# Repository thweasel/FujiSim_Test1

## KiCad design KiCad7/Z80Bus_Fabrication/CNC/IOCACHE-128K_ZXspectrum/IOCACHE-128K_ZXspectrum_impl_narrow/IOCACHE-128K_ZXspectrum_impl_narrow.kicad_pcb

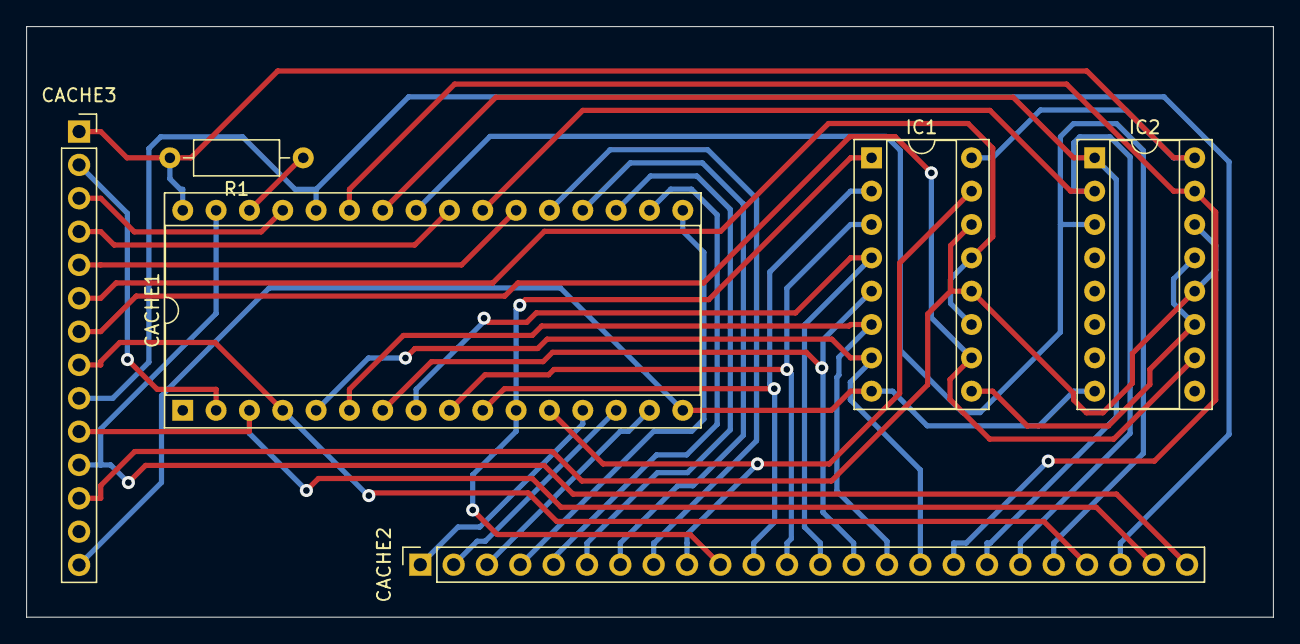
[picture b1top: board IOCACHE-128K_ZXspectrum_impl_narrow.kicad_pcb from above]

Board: 2 copper layers, 95.0 x 45.0 mm, 6 parts (0 on the bottom side), 35 nets.

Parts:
CACHE1: AS6C1008-55PCN; DIP-32_W15.24mm_Socket
CACHE2: Conn_01x24_Socket; PinSocket_1x24_P2.54mm_Vertical
CACHE3: Conn_01x14_Socket; PinSocket_1x14_P2.54mm_Vertical
IC1, IC2: 74HC590N; DIP-16_W7.62mm_Socket
R1: 10K; R_Axial_DIN0207_L6.3mm_D2.5mm_P10.16mm_Horizontal

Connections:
+5V: CACHE1.32 (VCC), CACHE3.1, IC1.16 (VCC), IC2.16 (VCC), R1.2
/IOCACHE-128K_ZXspectrum/CACHE_CE2: CACHE1.30 (CE2#), R1.1
/IOCACHE-128K_ZXspectrum/CACHE_CONTROL.A16: CACHE1.2 (A16), CACHE3.2
/IOCACHE-128K_ZXspectrum/CACHE_CONTROL.CS: CACHE1.22 (CE#), CACHE3.5
/IOCACHE-128K_ZXspectrum/CACHE_CONTROL.DATASTATUS+PERM_Z80_IORQ: CACHE3.6, IC1.11 (CPC), IC1.13 (CPR)
/IOCACHE-128K_ZXspectrum/CACHE_CONTROL.OE: CACHE1.24 (OE#), CACHE3.4
/IOCACHE-128K_ZXspectrum/CACHE_CONTROL.WE: CACHE1.29 (WE#), CACHE3.3
/IOCACHE-128K_ZXspectrum/CACHE_DATASTATUS: CACHE3.12, IC1.12 (~CE), IC1.14 (~OE), IC2.12 (~CE), IC2.14 (~OE)
/IOCACHE-128K_ZXspectrum/LOCAL_A0: CACHE1.12 (A0), CACHE2.9, IC1.15 (Q0)
/IOCACHE-128K_ZXspectrum/LOCAL_A1: CACHE1.11 (A1), CACHE2.10, IC1.1 (Q1)
/IOCACHE-128K_ZXspectrum/LOCAL_A2: CACHE1.10 (A2), CACHE2.11, IC1.2 (Q2)
/IOCACHE-128K_ZXspectrum/LOCAL_A3: CACHE1.9 (A3), CACHE2.12, IC1.3 (Q3)
/IOCACHE-128K_ZXspectrum/LOCAL_A4: CACHE1.8 (A4), CACHE2.13, IC1.4 (Q4)
/IOCACHE-128K_ZXspectrum/LOCAL_A5: CACHE1.7 (A5), CACHE2.14, IC1.5 (Q5)
/IOCACHE-128K_ZXspectrum/LOCAL_A6: CACHE1.6 (A6), CACHE2.15, IC1.6 (Q6)
/IOCACHE-128K_ZXspectrum/LOCAL_A7: CACHE1.5 (A7), CACHE2.16, IC1.7 (Q7)
/IOCACHE-128K_ZXspectrum/LOCAL_A8: CACHE1.27 (A8), CACHE2.17, IC2.15 (Q0)
/IOCACHE-128K_ZXspectrum/LOCAL_A9: CACHE1.26 (A9), CACHE2.18, IC2.1 (Q1)
/IOCACHE-128K_ZXspectrum/LOCAL_A10: CACHE1.23 (A10), CACHE2.19, IC2.2 (Q2)
/IOCACHE-128K_ZXspectrum/LOCAL_A11: CACHE1.25 (A11), CACHE2.20, IC2.3 (Q3)
/IOCACHE-128K_ZXspectrum/LOCAL_A12: CACHE1.4 (A12), CACHE2.21, CACHE3.8
/IOCACHE-128K_ZXspectrum/LOCAL_A13: CACHE1.28 (A13), CACHE2.22, CACHE3.9
/IOCACHE-128K_ZXspectrum/LOCAL_A14: CACHE1.3 (A14), CACHE2.23, CACHE3.10
/IOCACHE-128K_ZXspectrum/LOCAL_A15: CACHE1.31 (A15), CACHE2.24, CACHE3.11
/IOCACHE-128K_ZXspectrum/LOCAL_D0: CACHE1.13 (DQ0), CACHE2.1
/IOCACHE-128K_ZXspectrum/LOCAL_D1: CACHE1.14 (DQ1), CACHE2.2
/IOCACHE-128K_ZXspectrum/LOCAL_D2: CACHE1.15 (DQ2), CACHE2.3
/IOCACHE-128K_ZXspectrum/LOCAL_D3: CACHE1.17 (DQ3), CACHE2.4
/IOCACHE-128K_ZXspectrum/LOCAL_D4: CACHE1.18 (DQ4), CACHE2.5
/IOCACHE-128K_ZXspectrum/LOCAL_D5: CACHE1.19 (DQ5), CACHE2.6
/IOCACHE-128K_ZXspectrum/LOCAL_D6: CACHE1.20 (DQ6), CACHE2.7
/IOCACHE-128K_ZXspectrum/LOCAL_D7: CACHE1.21 (DQ7), CACHE2.8
/IOCACHE-128K_ZXspectrum/Z80_HARDLOCK: CACHE3.7, IC1.10 (~MRC), IC2.10 (~MRC)
GND: CACHE1.16 (VSS), CACHE3.14, IC1.8 (GND), IC2.8 (GND)
unnamed: IC1.9 (~RCO), IC2.11 (CPC), IC2.13 (CPR)

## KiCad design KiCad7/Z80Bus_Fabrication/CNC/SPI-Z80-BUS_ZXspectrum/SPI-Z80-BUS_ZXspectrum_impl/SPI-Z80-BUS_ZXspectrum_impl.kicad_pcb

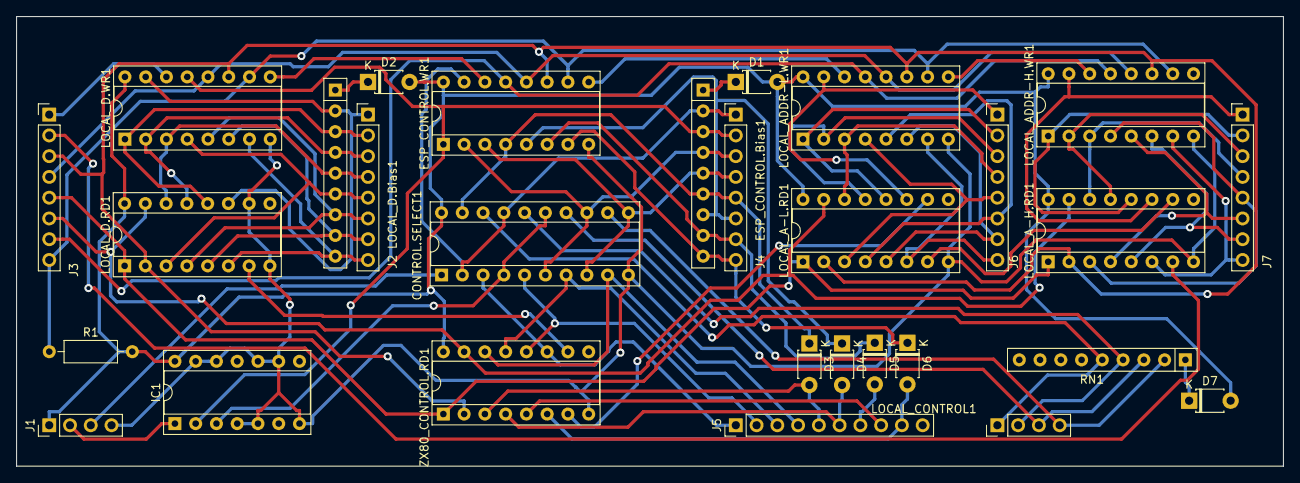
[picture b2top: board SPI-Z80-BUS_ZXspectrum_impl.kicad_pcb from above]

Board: 2 copper layers, 155.0 x 55.0 mm, 29 parts (0 on the bottom side), 67 nets.

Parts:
CONTROL.SELECT1: 74HC244N; DIP-20_W7.62mm_Socket
D1, D2, D3, D4, D5, D6, D7: 1N4148; D_T-1_P5.08mm_Horizontal
ESP_CONTROL.Bias1: 4609M-101-103LF; R_Array_SIP9
ESP_CONTROL.WR1: 74595N; DIP-16_W7.62mm_Socket
IC1: 74HC32N; DIP-14_W7.62mm_Socket
J1: PinHeader_2.54mm; PinHeader_1x04_P2.54mm_Vertical
J2: LOCAL_D; PinHeader_1x08_P2.54mm_Vertical
J3: ESP_SPI_INT; PinHeader_1x08_P2.54mm_Vertical
J4: ESP_CONTROL; PinHeader_1x08_P2.54mm_Vertical
J5: Z80_CONTROL; PinHeader_1x10_P2.54mm_Vertical
J6: LOCAL_A-L; PinHeader_1x08_P2.54mm_Vertical
J7: LOCAL_A-H; PinHeader_1x08_P2.54mm_Vertical
LOCAL_A-H.RD1: 74HC165N; DIP-16_W7.62mm_Socket
LOCAL_A-L.RD1: 74HC165N; DIP-16_W7.62mm_Socket
LOCAL_ADDR-H.WR1: 74595N; DIP-16_W7.62mm_Socket
LOCAL_ADDR-L.WR1: 74595N; DIP-16_W7.62mm_Socket
LOCAL_CONTROL1: LOCAL_CONTROL; PinHeader_1x04_P2.54mm_Vertical
LOCAL_D.Bias1: 4609M-101-103LF; R_Array_SIP9
LOCAL_D.RD1: 74HC165N; DIP-16_W7.62mm_Socket
LOCAL_D.WR1: 74595N; DIP-16_W7.62mm_Socket
R1: 22K; R_Axial_DIN0207_L6.3mm_D2.5mm_P10.16mm_Horizontal
RN1: LOCAL_CONTROL.Bias; R_Array_SIP9
ZX80_CONTROL.RD1: 74HC165N; DIP-16_W7.62mm_Socket

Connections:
+5V: CONTROL.SELECT1.20 (VCC), D1.2 (A), D2.2 (A), D7.2 (A), ESP_CONTROL.WR1.16 (VCC), IC1.14 (VCC), J1.1, LOCAL_A-H.RD1.16 (VCC), LOCAL_A-L.RD1.16 (VCC), LOCAL_ADDR-H.WR1.16 (VCC), LOCAL_ADDR-L.WR1.16 (VCC), LOCAL_D.RD1.16 (VCC), LOCAL_D.WR1.16 (VCC), R1.2, ZX80_CONTROL.RD1.16 (VCC)
/SPI-Z80-BUS/!ESP_HARDLOCK: CONTROL.SELECT1.1 (1OE), J1.3
/SPI-Z80-BUS/ESP_CONTROL.BUSRQ: CONTROL.SELECT1.19 (2OE), D3.1 (K), ESP_CONTROL.Bias1.6 (R5), ESP_CONTROL.WR1.4 (QE), J4.5
/SPI-Z80-BUS/ESP_CONTROL.IORQ: CONTROL.SELECT1.6 (1A2), CONTROL.SELECT1.13 (2A2), ESP_CONTROL.Bias1.4 (R3), ESP_CONTROL.WR1.2 (QC), J4.3
/SPI-Z80-BUS/ESP_CONTROL.MEMRQ: CONTROL.SELECT1.8 (1A3), CONTROL.SELECT1.11 (2A3), ESP_CONTROL.Bias1.5 (R4), ESP_CONTROL.WR1.3 (QD), J4.4
/SPI-Z80-BUS/ESP_CONTROL.NMI: D6.1 (K), ESP_CONTROL.Bias1.9 (R8), ESP_CONTROL.WR1.7 (QH), J4.8
/SPI-Z80-BUS/ESP_CONTROL.RD: CONTROL.SELECT1.2 (1A0), CONTROL.SELECT1.17 (2A0), ESP_CONTROL.Bias1.2 (R1), ESP_CONTROL.WR1.15 (QA), J4.1
/SPI-Z80-BUS/ESP_CONTROL.ROMCS: D5.1 (K), ESP_CONTROL.Bias1.8 (R7), ESP_CONTROL.WR1.6 (QG), J4.7
/SPI-Z80-BUS/ESP_CONTROL.WAIT: D4.1 (K), ESP_CONTROL.Bias1.7 (R6), ESP_CONTROL.WR1.5 (QF), J4.6
/SPI-Z80-BUS/ESP_CONTROL.WR: ESP_CONTROL.Bias1.3 (R2), ESP_CONTROL.WR1.1 (QB), IC1.2, J4.2, LOCAL_D.WR1.13 (~OE)
/SPI-Z80-BUS/ESP_PULSE: IC1.1, J1.2
/SPI-Z80-BUS/ESP_SPI_INT.CE: J3.6, LOCAL_A-H.RD1.15 (~CE), LOCAL_A-L.RD1.15 (~CE), LOCAL_D.RD1.15 (~CE), ZX80_CONTROL.RD1.15 (~CE)
/SPI-Z80-BUS/ESP_SPI_INT.MISO: J3.2, LOCAL_A-H.RD1.7 (~Q7)
/SPI-Z80-BUS/ESP_SPI_INT.MOSI: J3.1, LOCAL_D.WR1.14 (SER)
/SPI-Z80-BUS/ESP_SPI_INT.MR: ESP_CONTROL.WR1.10 (~SRCLR), J3.8, LOCAL_ADDR-H.WR1.10 (~SRCLR), LOCAL_ADDR-L.WR1.10 (~SRCLR), LOCAL_D.WR1.10 (~SRCLR), R1.1
/SPI-Z80-BUS/ESP_SPI_INT.OE: ESP_CONTROL.WR1.13 (~OE), J3.7, LOCAL_ADDR-H.WR1.13 (~OE), LOCAL_ADDR-L.WR1.13 (~OE)
/SPI-Z80-BUS/ESP_SPI_INT.PL: J3.5, LOCAL_A-H.RD1.1 (~PL), LOCAL_A-L.RD1.1 (~PL), LOCAL_D.RD1.1 (~PL), ZX80_CONTROL.RD1.1 (~PL)
/SPI-Z80-BUS/ESP_SPI_INT.SCK: ESP_CONTROL.WR1.11 (SRCLK), J3.3, LOCAL_A-H.RD1.2 (CP), LOCAL_A-L.RD1.2 (CP), LOCAL_ADDR-H.WR1.11 (SRCLK), LOCAL_ADDR-L.WR1.11 (SRCLK), LOCAL_D.RD1.2 (CP), LOCAL_D.WR1.11 (SRCLK), ZX80_CONTROL.RD1.2 (CP)
/SPI-Z80-BUS/ESP_SPI_INT.STC: ESP_CONTROL.WR1.12 (RCLK), J3.4, LOCAL_ADDR-H.WR1.12 (RCLK), LOCAL_ADDR-L.WR1.12 (RCLK), LOCAL_D.WR1.12 (RCLK)
/SPI-Z80-BUS/LOCAL_A0: J6.1, LOCAL_A-L.RD1.11 (D0), LOCAL_ADDR-L.WR1.15 (QA)
/SPI-Z80-BUS/LOCAL_A1: J6.2, LOCAL_A-L.RD1.12 (D1), LOCAL_ADDR-L.WR1.1 (QB)
/SPI-Z80-BUS/LOCAL_A2: J6.3, LOCAL_A-L.RD1.13 (D2), LOCAL_ADDR-L.WR1.2 (QC)
/SPI-Z80-BUS/LOCAL_A3: J6.4, LOCAL_A-L.RD1.14 (D3), LOCAL_ADDR-L.WR1.3 (QD)
/SPI-Z80-BUS/LOCAL_A4: J6.5, LOCAL_A-L.RD1.3 (D4), LOCAL_ADDR-L.WR1.4 (QE)
/SPI-Z80-BUS/LOCAL_A5: J6.6, LOCAL_A-L.RD1.4 (D5), LOCAL_ADDR-L.WR1.5 (QF)
/SPI-Z80-BUS/LOCAL_A6: J6.7, LOCAL_A-L.RD1.5 (D6), LOCAL_ADDR-L.WR1.6 (QG)
/SPI-Z80-BUS/LOCAL_A7: J6.8, LOCAL_A-L.RD1.6 (D7), LOCAL_ADDR-L.WR1.7 (QH)
/SPI-Z80-BUS/LOCAL_A8: J7.1, LOCAL_A-H.RD1.11 (D0), LOCAL_ADDR-H.WR1.15 (QA)
/SPI-Z80-BUS/LOCAL_A9: J7.2, LOCAL_A-H.RD1.12 (D1), LOCAL_ADDR-H.WR1.1 (QB)
/SPI-Z80-BUS/LOCAL_A10: J7.3, LOCAL_A-H.RD1.13 (D2), LOCAL_ADDR-H.WR1.2 (QC)
/SPI-Z80-BUS/LOCAL_A11: J7.4, LOCAL_A-H.RD1.14 (D3), LOCAL_ADDR-H.WR1.3 (QD)
/SPI-Z80-BUS/LOCAL_A12: J7.5, LOCAL_A-H.RD1.3 (D4), LOCAL_ADDR-H.WR1.4 (QE)
/SPI-Z80-BUS/LOCAL_A13: J7.6, LOCAL_A-H.RD1.4 (D5), LOCAL_ADDR-H.WR1.5 (QF)
/SPI-Z80-BUS/LOCAL_A14: J7.7, LOCAL_A-H.RD1.5 (D6), LOCAL_ADDR-H.WR1.6 (QG)
/SPI-Z80-BUS/LOCAL_A15: J7.8, LOCAL_A-H.RD1.6 (D7), LOCAL_ADDR-H.WR1.7 (QH)
/SPI-Z80-BUS/LOCAL_CONTROL.IORQ: CONTROL.SELECT1.14 (1Y2), LOCAL_CONTROL1.3, RN1.3 (R2)
/SPI-Z80-BUS/LOCAL_CONTROL.MEMRQ: CONTROL.SELECT1.12 (1Y3), LOCAL_CONTROL1.4, RN1.2 (R1)
/SPI-Z80-BUS/LOCAL_CONTROL.RD: CONTROL.SELECT1.18 (1Y0), LOCAL_CONTROL1.1, RN1.5 (R4)
/SPI-Z80-BUS/LOCAL_CONTROL.WR: CONTROL.SELECT1.16 (1Y1), LOCAL_CONTROL1.2, RN1.4 (R3)
/SPI-Z80-BUS/LOCAL_D0: J2.1, LOCAL_D.Bias1.2 (R1), LOCAL_D.RD1.11 (D0), LOCAL_D.WR1.15 (QA)
/SPI-Z80-BUS/LOCAL_D1: J2.2, LOCAL_D.Bias1.3 (R2), LOCAL_D.RD1.12 (D1), LOCAL_D.WR1.1 (QB)
/SPI-Z80-BUS/LOCAL_D2: J2.3, LOCAL_D.Bias1.4 (R3), LOCAL_D.RD1.13 (D2), LOCAL_D.WR1.2 (QC)
/SPI-Z80-BUS/LOCAL_D3: J2.4, LOCAL_D.Bias1.5 (R4), LOCAL_D.RD1.14 (D3), LOCAL_D.WR1.3 (QD)
/SPI-Z80-BUS/LOCAL_D4: J2.5, LOCAL_D.Bias1.6 (R5), LOCAL_D.RD1.3 (D4), LOCAL_D.WR1.4 (QE)
/SPI-Z80-BUS/LOCAL_D5: J2.6, LOCAL_D.Bias1.7 (R6), LOCAL_D.RD1.4 (D5), LOCAL_D.WR1.5 (QF)
/SPI-Z80-BUS/LOCAL_D6: J2.7, LOCAL_D.Bias1.8 (R7), LOCAL_D.RD1.5 (D6), LOCAL_D.WR1.6 (QG)
/SPI-Z80-BUS/LOCAL_D7: J2.8, LOCAL_D.Bias1.9 (R8), LOCAL_D.RD1.6 (D7), LOCAL_D.WR1.7 (QH)
/SPI-Z80-BUS/Z80_CONTROL.BUSACK: J5.8, ZX80_CONTROL.RD1.5 (D6)
/SPI-Z80-BUS/Z80_CONTROL.BUSRQ: D3.2 (A), J5.5, ZX80_CONTROL.RD1.3 (D4)
/SPI-Z80-BUS/Z80_CONTROL.IORQ: CONTROL.SELECT1.7 (2Y2), J5.3, ZX80_CONTROL.RD1.13 (D2)
/SPI-Z80-BUS/Z80_CONTROL.MEMRQ: CONTROL.SELECT1.9 (2Y3), J5.4, ZX80_CONTROL.RD1.14 (D3)
/SPI-Z80-BUS/Z80_CONTROL.NMI: D6.2 (A), J5.9, ZX80_CONTROL.RD1.6 (D7)
/SPI-Z80-BUS/Z80_CONTROL.RD: CONTROL.SELECT1.3 (2Y0), J5.1, ZX80_CONTROL.RD1.11 (D0)
/SPI-Z80-BUS/Z80_CONTROL.ROMCS: D5.2 (A), J5.7
/SPI-Z80-BUS/Z80_CONTROL.WAIT: D4.2 (A), J5.6, ZX80_CONTROL.RD1.4 (D5)
/SPI-Z80-BUS/Z80_CONTROL.WR: CONTROL.SELECT1.5 (2Y1), J5.2, ZX80_CONTROL.RD1.12 (D1)
GND: CONTROL.SELECT1.10 (GND), ESP_CONTROL.WR1.8 (GND), IC1.4, IC1.5, IC1.7 (GND), IC1.9, IC1.10, IC1.12, IC1.13, J1.4, LOCAL_A-H.RD1.8 (GND), LOCAL_A-L.RD1.8 (GND), LOCAL_ADDR-H.WR1.8 (GND), LOCAL_ADDR-L.WR1.8 (GND), LOCAL_D.RD1.8 (GND), LOCAL_D.RD1.10 (DS), LOCAL_D.WR1.8 (GND), ZX80_CONTROL.RD1.8 (GND)
unnamed: CONTROL.SELECT1.4 (1A1), CONTROL.SELECT1.15 (2A1), IC1.3
unnamed: D1.1 (K), ESP_CONTROL.Bias1.1 (common)
unnamed: D2.1 (K), LOCAL_D.Bias1.1 (common)
unnamed: D7.1 (K), RN1.1 (common)
unnamed: ESP_CONTROL.WR1.9 (QH'), LOCAL_ADDR-L.WR1.14 (SER)
unnamed: ESP_CONTROL.WR1.14 (SER), LOCAL_D.WR1.9 (QH')
unnamed: LOCAL_A-H.RD1.10 (DS), LOCAL_A-L.RD1.7 (~Q7)
unnamed: LOCAL_A-L.RD1.10 (DS), ZX80_CONTROL.RD1.7 (~Q7)
unnamed: LOCAL_ADDR-H.WR1.14 (SER), LOCAL_ADDR-L.WR1.9 (QH')
unnamed: LOCAL_D.RD1.7 (~Q7), ZX80_CONTROL.RD1.10 (DS)

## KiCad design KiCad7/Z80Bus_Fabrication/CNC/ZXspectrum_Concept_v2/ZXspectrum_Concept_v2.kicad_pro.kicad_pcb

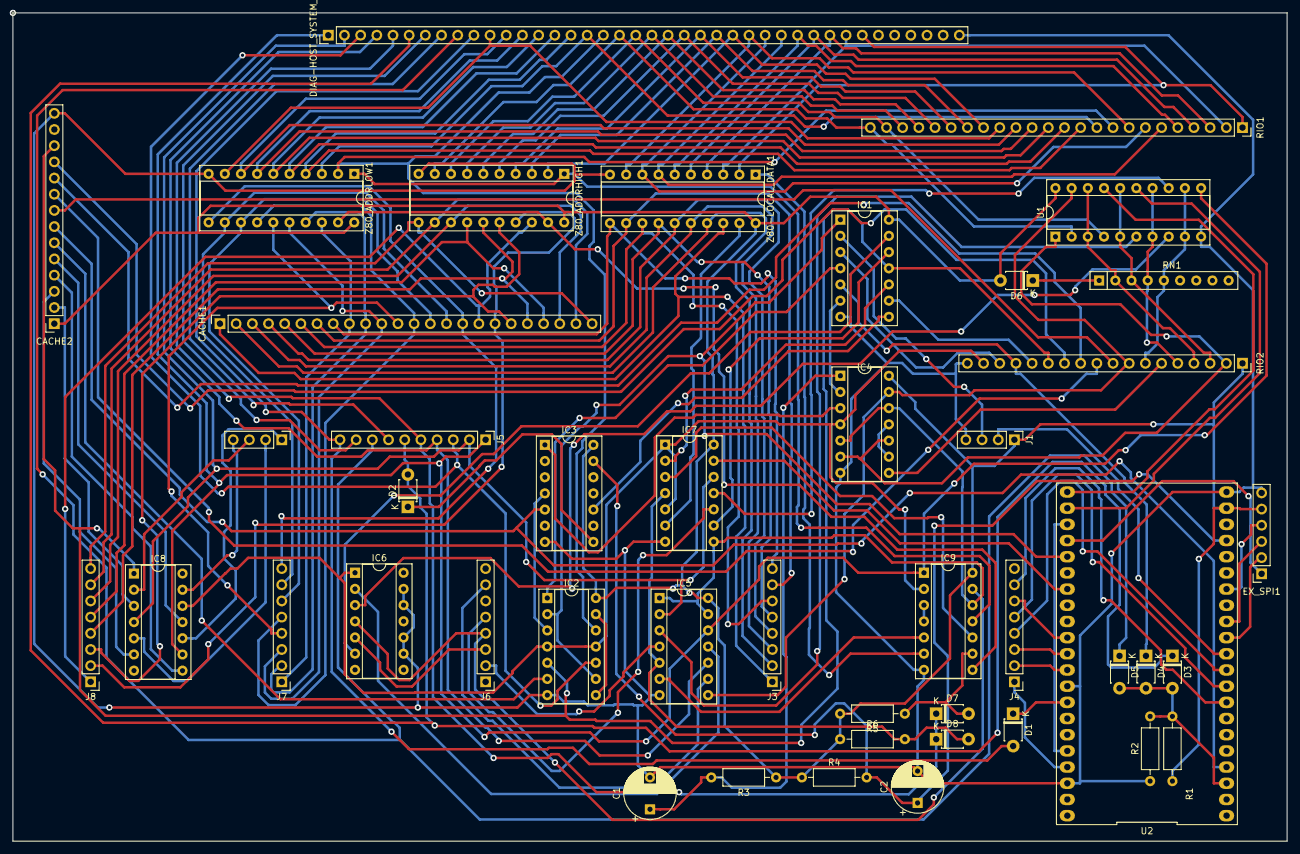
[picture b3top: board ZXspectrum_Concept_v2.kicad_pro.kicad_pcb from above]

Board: 2 copper layers, 200.0 x 130.0 mm, 45 parts (0 on the bottom side), 139 nets.

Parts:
C1, C2: 10UF; CP_Radial_D8.0mm_P5.00mm
CACHE1: Conn_01x24_Socket; PinSocket_1x24_P2.54mm_Vertical
CACHE2: Conn_01x14_Socket; PinSocket_1x14_P2.54mm_Vertical
D1, D2, D3, D4, D5, D6, D7, D8: 1N4148; D_T-1_P5.08mm_Horizontal
DIAG-HOST_SYSTEM_BUS1: DIAG-HOST_SYSTEM_BUS; PinHeader_1x40_P2.54mm_Vertical
EX_SPI1: PinSocket_2.54mm; PinSocket_1x06_P2.54mm_Vertical
IC1: 7404N; DIP-14_W7.62mm_Socket
IC2, IC5, IC7, IC9: 74HC32N; DIP-14_W7.62mm_Socket
IC3: 7474N; DIP-14_W7.62mm_Socket
IC4, IC6, IC8: 74HC08N; DIP-14_W7.62mm_Socket
J1: PinHeader_2.54mm; PinHeader_1x04_P2.54mm_Vertical
J3: LOCAL_D; PinHeader_1x08_P2.54mm_Vertical
J4: ESP_SPI_INT; PinHeader_1x08_P2.54mm_Vertical
J5: Z80_CONTROL; PinHeader_1x10_P2.54mm_Vertical
J6: ESP_CONTROL; PinHeader_1x08_P2.54mm_Vertical
J7: LOCAL_A-L; PinHeader_1x08_P2.54mm_Vertical
J8: LOCAL_A-H; PinHeader_1x08_P2.54mm_Vertical
LOCAL_CONTROL1: LOCAL_CONTROL; PinHeader_1x04_P2.54mm_Vertical
R1, R2, R3, R4: 22K; R_Axial_DIN0207_L6.3mm_D2.5mm_P10.16mm_Horizontal
R5, R6: 10K; R_Axial_DIN0207_L6.3mm_D2.5mm_P10.16mm_Horizontal
RIO1: Conn_01x24_Socket; PinSocket_1x24_P2.54mm_Vertical
RIO2: Conn_01x18_Socket; PinSocket_1x18_P2.54mm_Vertical
RN1: 4609M-101-103LF; R_Array_SIP9
U1: 74HC244N; DIP-20_W7.62mm_Socket
U2: FREENOVE_ESP32-WROVER-DEV
Z80-LOCAL_DATA1, Z80_ADDRHIGH1, Z80_ADDRLOW1: 74HC245N; DIP-20_W7.62mm_Socket

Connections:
+5V: CACHE2.1, D6.2 (A), EX_SPI1.5, IC1.14 (VCC), IC2.14 (VCC), IC3.14 (VCC), IC4.14 (VCC), IC5.14 (VCC), IC7.14 (VCC), IC9.14 (VCC), J1.1, R1.2, R3.1, R4.1, R5.2, R6.1, RIO2.1, U1.20 (VCC), U2.20 (+5V), Z80-LOCAL_DATA1.20 (VCC), Z80_ADDRHIGH1.20 (VCC), Z80_ADDRLOW1.20 (VCC)
/CACHE connector/CACHE_CONTROL.A16: CACHE2.2, IC8.3
/CACHE connector/CACHE_CONTROL.CS: CACHE2.5, IC8.11
/CACHE connector/CACHE_CONTROL.DATASTATUS+PERM_Z80_IORQ: CACHE2.6, IC2.6
/CACHE connector/CACHE_CONTROL.OE: CACHE2.4, IC8.8
/CACHE connector/CACHE_CONTROL.WE: CACHE2.3, IC8.6
/CACHE connector/CACHE_DATASTATUS: CACHE2.12, IC1.11, IC2.5, IC8.1, RIO2.13
/CACHE connector/CACHE_SEL_0: CACHE2.8, RIO2.9
/CACHE connector/CACHE_SEL_1: CACHE2.9, RIO2.10
/CACHE connector/CACHE_SEL_2: CACHE2.10, RIO2.11
/CACHE connector/CACHE_SEL_3: CACHE2.11, RIO2.12
/CACHE connector/LOCAL_A0: CACHE1.9, J7.1, Z80_ADDRLOW1.18 (B0)
/CACHE connector/LOCAL_A1: CACHE1.10, J7.2, Z80_ADDRLOW1.17 (B1)
/CACHE connector/LOCAL_A2: CACHE1.11, J7.3, Z80_ADDRLOW1.16 (B2)
/CACHE connector/LOCAL_A3: CACHE1.12, J7.4, Z80_ADDRLOW1.15 (B3)
/CACHE connector/LOCAL_A4: CACHE1.13, J7.5, Z80_ADDRLOW1.14 (B4)
/CACHE connector/LOCAL_A5: CACHE1.14, J7.6, Z80_ADDRLOW1.13 (B5)
/CACHE connector/LOCAL_A6: CACHE1.15, J7.7, Z80_ADDRLOW1.12 (B6)
/CACHE connector/LOCAL_A7: CACHE1.16, J7.8, Z80_ADDRLOW1.11 (B7)
/CACHE connector/LOCAL_A8: CACHE1.17, J8.1, Z80_ADDRHIGH1.18 (B0)
/CACHE connector/LOCAL_A9: CACHE1.18, J8.2, Z80_ADDRHIGH1.17 (B1)
/CACHE connector/LOCAL_A10: CACHE1.19, J8.3, Z80_ADDRHIGH1.16 (B2)
/CACHE connector/LOCAL_A11: CACHE1.20, J8.4, Z80_ADDRHIGH1.15 (B3)
/CACHE connector/LOCAL_A12: CACHE1.21, J8.5, Z80_ADDRHIGH1.14 (B4)
/CACHE connector/LOCAL_A13: CACHE1.22, J8.6, Z80_ADDRHIGH1.13 (B5)
/CACHE connector/LOCAL_A14: CACHE1.23, J8.7, Z80_ADDRHIGH1.12 (B6)
/CACHE connector/LOCAL_A15: CACHE1.24, J8.8, Z80_ADDRHIGH1.11 (B7)
/CACHE connector/LOCAL_D0: CACHE1.1, J3.1, Z80-LOCAL_DATA1.18 (B0)
/CACHE connector/LOCAL_D1: CACHE1.2, J3.2, Z80-LOCAL_DATA1.17 (B1)
/CACHE connector/LOCAL_D2: CACHE1.3, J3.3, Z80-LOCAL_DATA1.16 (B2)
/CACHE connector/LOCAL_D3: CACHE1.4, J3.4, Z80-LOCAL_DATA1.15 (B3)
/CACHE connector/LOCAL_D4: CACHE1.5, J3.5, Z80-LOCAL_DATA1.14 (B4)
/CACHE connector/LOCAL_D5: CACHE1.6, J3.6, Z80-LOCAL_DATA1.13 (B5)
/CACHE connector/LOCAL_D6: CACHE1.7, J3.7, Z80-LOCAL_DATA1.12 (B6)
/CACHE connector/LOCAL_D7: CACHE1.8, J3.8, Z80-LOCAL_DATA1.11 (B7)
/CACHE connector/Z80_HARDLOCK: CACHE2.7, IC3.5 (Q), U2.4 (GPIO39)
/CORE/ESP_HARDLOCK: IC1.1, IC2.2, IC2.9, U2.26 (GPIO2)
/CORE/ESP_INT: D3.2 (A), D4.2 (A), D5.2 (A), R1.1, R2.2, U2.3 (GPIO36)
/CORE/ESP_PULSE: J1.2, U2.11 (GPIO27)
/CORE/ESP_ROMSEL_0: U1.15 (2A1), U2.23 (GPIO7)
/CORE/ESP_ROMSEL_1: U1.17 (2A0), U2.22 (GPIO6)
/CORE/ESP_ROM_WR_PROTECT: IC7.13, U2.28 (GPIO4)
/CORE/ESP_SPI_INT.CE: J4.6, U2.31 (GPIO5)
/CORE/ESP_SPI_INT.MISO: J4.2, U2.33 (GPIO19)
/CORE/ESP_SPI_INT.MOSI: J4.1, U2.39 (GPIO23)
/CORE/ESP_SPI_INT.OE: J4.7, U2.8 (GPIO33)
/CORE/ESP_SPI_INT.PL: J4.5, U2.9 (GPIO25)
/CORE/ESP_SPI_INT.SCK: J4.3, U2.32 (GPIO18)
/CORE/ESP_SPI_INT.STC: J4.4, U2.10 (GPIO26)
/CORE/ESP_WAIT_RESET: C2.1, IC3.13 (~R), R4.2, U2.18 (GPIO11)
/CORE/EX_MISO: EX_SPI1.3, U2.13 (GPIO12)
/CORE/EX_MOSI: EX_SPI1.4, U2.15 (GPIO13)
/CORE/EX_SCK: EX_SPI1.2, U2.12 (GPIO14)
/CORE/EX_SS: EX_SPI1.1, U2.25 (GPIO8)
/CORE/SD_CARD_SS: U2.24 (GPIO15), U2.38 (GPIO22)
/CORE/Z80_HARDLOCK_RESET: D4.1 (K), IC1.5, RIO2.15
/GLUE/!ESP_HARDLOCK: IC1.2, J1.3
/GLUE/CLR_Z80_HARDLOCK: IC3.1 (~R), IC4.3
/GLUE/ESP_IOD_CONFIG: IC4.5, IC4.12, IC5.1, IC5.13, IC7.8, IC9.12
/GLUE/PERM_Z80_IORQ: IC2.4, IC2.11, IC4.4, IC6.1, IC7.1, IC7.5, IC8.12, IC9.2, RIO2.17
/GLUE/PRE_Z80_HARDLOCK: IC2.3, IC3.4 (~S)
/GLUE/RIO CONTROL/ROM_WR_PROTECT+Z80_WR: IC7.11, U1.13 (2A2)
/GLUE/RIO CONTROL/Z80_RD+ESP_IOD_CONFIG+PERM_Z80_IORQ: IC6.3, U1.8 (1A3)
/GLUE/RIO CONTROL/Z80_WR+ESP_IOD_CONFIG: IC5.3, U1.6 (1A2)
/GLUE/RIO_CONTROL.A14: RIO2.4, RN1.2 (R1), U1.3 (2Y0), U1.18 (1Y0)
/GLUE/RIO_CONTROL.A15: RIO2.3, RN1.3 (R2), U1.5 (2Y1), U1.16 (1Y1)
/GLUE/RIO_CONTROL.A16: IC4.6, IC4.10, RIO2.2, U1.1 (1OE)
/GLUE/RIO_CONTROL.CE: IC4.8, RIO2.6
/GLUE/RIO_CONTROL.OE: RIO2.7, RN1.5 (R4), U1.9 (2Y3), U1.12 (1Y3)
/GLUE/RIO_CONTROL.ROM_RDY: IC4.13, IC5.8, RIO2.8, U1.19 (2OE)
/GLUE/RIO_CONTROL.WE: RIO2.5, RN1.4 (R3), U1.7 (2Y2), U1.14 (1Y2)
/GLUE/WAIT_IO: IC1.9, RIO2.14
/GLUE/Z80 BUS CONTROL/!CACHE_DATASTATUS: IC1.10, IC7.2
/GLUE/Z80 BUS CONTROL/Z80_ADD_CONNECT: D7.2 (A), IC9.9, R5.1
/GLUE/Z80 BUS CONTROL/Z80_DATA_CONNECT: D8.2 (A), IC5.5, IC7.4, R6.2
/GLUE/Z80_BUS_CONTROL.Z80_ADD_DIR: IC9.11, Z80_ADDRHIGH1.1 (A->B), Z80_ADDRLOW1.1 (A->B)
/GLUE/Z80_BUS_CONTROL.Z80_ADD_OE: IC9.8, Z80_ADDRHIGH1.19 (CE), Z80_ADDRLOW1.19 (CE)
/GLUE/Z80_BUS_CONTROL.Z80_DATA_DIR: IC9.6, Z80-LOCAL_DATA1.1 (A->B)
/GLUE/Z80_BUS_CONTROL.Z80_DATA_OE: IC7.6, Z80-LOCAL_DATA1.19 (CE)
/GLUE/Z80_HARDLOCK_SET: IC1.3, RIO2.16
/RIO connector/Z80_A0: DIAG-HOST_SYSTEM_BUS1.18, IC2.12, RIO1.9, Z80_ADDRLOW1.2 (A0)
/RIO connector/Z80_A1: DIAG-HOST_SYSTEM_BUS1.17, RIO1.10, Z80_ADDRLOW1.3 (A1)
/RIO connector/Z80_A2: DIAG-HOST_SYSTEM_BUS1.16, RIO1.11, Z80_ADDRLOW1.4 (A2)
/RIO connector/Z80_A3: DIAG-HOST_SYSTEM_BUS1.15, RIO1.12, Z80_ADDRLOW1.5 (A3)
/RIO connector/Z80_A4: DIAG-HOST_SYSTEM_BUS1.14, RIO1.13, Z80_ADDRLOW1.6 (A4)
/RIO connector/Z80_A5: DIAG-HOST_SYSTEM_BUS1.13, RIO1.14, Z80_ADDRLOW1.7 (A5)
/RIO connector/Z80_A6: DIAG-HOST_SYSTEM_BUS1.12, RIO1.15, Z80_ADDRLOW1.8 (A6)
/RIO connector/Z80_A7: DIAG-HOST_SYSTEM_BUS1.11, RIO1.16, Z80_ADDRLOW1.9 (A7)
/RIO connector/Z80_A8: DIAG-HOST_SYSTEM_BUS1.26, RIO1.17, Z80_ADDRHIGH1.2 (A0)
/RIO connector/Z80_A9: DIAG-HOST_SYSTEM_BUS1.25, RIO1.18, Z80_ADDRHIGH1.3 (A1)
/RIO connector/Z80_A10: DIAG-HOST_SYSTEM_BUS1.24, RIO1.19, Z80_ADDRHIGH1.4 (A2)
/RIO connector/Z80_A11: DIAG-HOST_SYSTEM_BUS1.23, RIO1.20, Z80_ADDRHIGH1.5 (A3)
/RIO connector/Z80_A12: DIAG-HOST_SYSTEM_BUS1.22, RIO1.21, Z80_ADDRHIGH1.6 (A4)
/RIO connector/Z80_A13: DIAG-HOST_SYSTEM_BUS1.21, RIO1.22, Z80_ADDRHIGH1.7 (A5)
/RIO connector/Z80_A14: DIAG-HOST_SYSTEM_BUS1.20, RIO1.23, U1.4 (1A1), Z80_ADDRHIGH1.8 (A6)
/RIO connector/Z80_A15: DIAG-HOST_SYSTEM_BUS1.19, RIO1.24, U1.2 (1A0), Z80_ADDRHIGH1.9 (A7)
/RIO connector/Z80_D0: DIAG-HOST_SYSTEM_BUS1.34, RIO1.1, Z80-LOCAL_DATA1.2 (A0)
/RIO connector/Z80_D1: DIAG-HOST_SYSTEM_BUS1.33, RIO1.2, Z80-LOCAL_DATA1.3 (A1)
/RIO connector/Z80_D2: DIAG-HOST_SYSTEM_BUS1.32, RIO1.3, Z80-LOCAL_DATA1.4 (A2)
/RIO connector/Z80_D3: DIAG-HOST_SYSTEM_BUS1.31, RIO1.4, Z80-LOCAL_DATA1.5 (A3)
/RIO connector/Z80_D4: DIAG-HOST_SYSTEM_BUS1.30, RIO1.5, Z80-LOCAL_DATA1.6 (A4)
/RIO connector/Z80_D5: DIAG-HOST_SYSTEM_BUS1.29, RIO1.6, Z80-LOCAL_DATA1.7 (A5)
/RIO connector/Z80_D6: DIAG-HOST_SYSTEM_BUS1.28, RIO1.7, Z80-LOCAL_DATA1.8 (A6)
/RIO connector/Z80_D7: DIAG-HOST_SYSTEM_BUS1.27, RIO1.8, Z80-LOCAL_DATA1.9 (A7)
/SPI connector/ESP_CONTROL.BUSRQ: IC7.10, J6.5
/SPI connector/ESP_CONTROL.IORQ: IC6.5, J6.3
/SPI connector/ESP_CONTROL.MEMRQ: IC6.4, IC9.13, J6.4
/SPI connector/ESP_CONTROL.ROMCS: IC5.9, J6.7
/SPI connector/ESP_CONTROL.WR: IC5.4, J6.2
/SPI connector/LOCAL_CONTROL.IORQ: IC8.2, LOCAL_CONTROL1.3
/SPI connector/LOCAL_CONTROL.MEMRQ: IC8.13, LOCAL_CONTROL1.4
/SPI connector/LOCAL_CONTROL.RD: IC8.10, LOCAL_CONTROL1.1
/SPI connector/LOCAL_CONTROL.WR: IC8.5, LOCAL_CONTROL1.2
/SPI connector/Z80_CONTROL.BUSACK: D5.1 (K), DIAG-HOST_SYSTEM_BUS1.9, J5.8
/SPI connector/Z80_CONTROL.BUSRQ: D7.1 (K), D8.1 (K), DIAG-HOST_SYSTEM_BUS1.5, J5.5
/SPI connector/Z80_CONTROL.IORQ: DIAG-HOST_SYSTEM_BUS1.3, IC2.10, J5.3
/SPI connector/Z80_CONTROL.MEMRQ: DIAG-HOST_SYSTEM_BUS1.4, IC5.10, J5.4
/SPI connector/Z80_CONTROL.NMI: DIAG-HOST_SYSTEM_BUS1.7, J5.9
/SPI connector/Z80_CONTROL.RD: DIAG-HOST_SYSTEM_BUS1.1, IC5.12, IC8.9, IC9.1, J5.1, U1.11 (2A3)
/SPI connector/Z80_CONTROL.RESET: D1.2 (A), DIAG-HOST_SYSTEM_BUS1.10, J5.10
/SPI connector/Z80_CONTROL.ROMCS: DIAG-HOST_SYSTEM_BUS1.8, J5.7
/SPI connector/Z80_CONTROL.WAIT: D2.2 (A), D3.1 (K), DIAG-HOST_SYSTEM_BUS1.6, J5.6
/SPI connector/Z80_CONTROL.WR: DIAG-HOST_SYSTEM_BUS1.2, IC5.2, IC7.12, IC8.4, J5.2
GND: C1.2, C2.2, CACHE2.14, DIAG-HOST_SYSTEM_BUS1.40, EX_SPI1.6, IC1.7 (GND), IC2.7 (GND), IC3.7 (GND), IC4.7 (GND), IC5.7 (GND), IC6.9, IC6.10, IC6.12, IC6.13, IC7.7 (GND), IC9.7 (GND), J1.4, R2.1, RIO2.18, U1.10 (GND), U2.21 (GND), U2.34 (GND), U2.40 (GND), Z80-LOCAL_DATA1.10 (GND), Z80_ADDRHIGH1.10 (GND), Z80_ADDRLOW1.10 (GND)
unnamed: C1.1, IC4.1, R3.2
unnamed: D1.1 (K), U2.35 (GPIO21)
unnamed: D2.1 (K), IC3.8 (~Q)
unnamed: D6.1 (K), RN1.1 (common)
unnamed: IC1.4, IC2.1
unnamed: IC1.6, IC4.2
unnamed: IC1.12, IC7.9
unnamed: IC1.13, IC6.6
unnamed: IC2.8, IC2.13
unnamed: IC1.8, IC3.10 (~S)
unnamed: IC4.9, IC4.11
unnamed: IC5.6, IC9.5
unnamed: IC5.11, IC6.2
unnamed: IC7.3, IC9.10
unnamed: IC9.3, IC9.4

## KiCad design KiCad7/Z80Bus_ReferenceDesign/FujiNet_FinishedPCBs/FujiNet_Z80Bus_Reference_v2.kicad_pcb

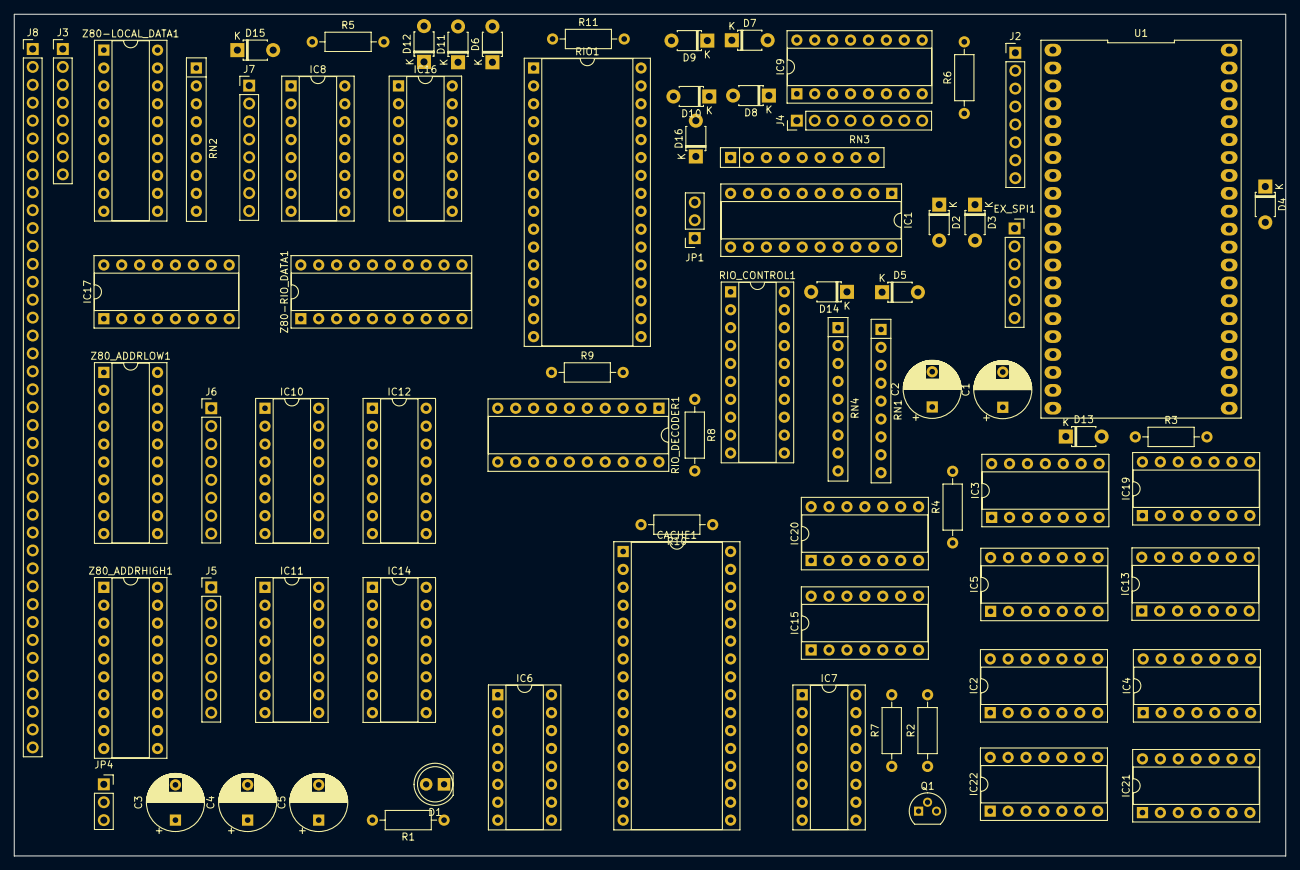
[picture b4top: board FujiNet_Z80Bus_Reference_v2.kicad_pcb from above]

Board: 2 copper layers, 180.3 x 119.4 mm, 77 parts (0 on the bottom side), 119 nets, no tracks yet.

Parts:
C1, C2: 10UF; CP_Radial_D8.0mm_P5.00mm
C3: 10 uf; CP_Radial_D8.0mm_P5.00mm
C4, C5: .1 uf; CP_Radial_D8.0mm_P5.00mm
CACHE1: AS6C1008-55PCN; DIP-32_W15.24mm_Socket
D1: POWER_LED; LED_D5.0mm
D2, D3, D4, D5, D6, D7, D8, D9, D10, D11, D12, D13, D14, D15, D16: 1N4148; D_T-1_P5.08mm_Horizontal
EX_SPI1: PINHD-1X6; PinSocket_1x06_P2.54mm_Vertical
IC1: 74244N; DIP-20_W7.62mm_Socket
IC2: 7404N; DIP-14_W7.62mm_Socket
IC3: 7474N; DIP-14_W7.62mm_Socket
IC4, IC13, IC19, IC21, IC22: 7432N; DIP-14_W7.62mm_Socket
IC5, IC15, IC20: 7408N; DIP-14_W7.62mm_Socket
IC6, IC7: 74590N; DIP-16_W7.62mm_Socket
IC8, IC9, IC10, IC11: 74595N; DIP-16_W7.62mm_Socket
IC12, IC14, IC16, IC17: 74165N; DIP-16_W7.62mm_Socket
J2: DIAG-ESP_SPI; PinHeader_1x08_P2.54mm_Vertical
J3: DIAG-Z80_CONTROL; PinHeader_1x08_P2.54mm_Vertical
J4: DIAG-ESP_CONTROL; PinHeader_1x08_P2.54mm_Vertical
J5: DIAG-LOCAL_ADD_HIGH; PinHeader_1x08_P2.54mm_Vertical
J6: DIAG-LOCAL_ADD_LOW; PinHeader_1x08_P2.54mm_Vertical
J7: DIAG-LOCAL_DATA; PinHeader_1x08_P2.54mm_Vertical
J8: DIAG-HOST_SYSTEM_BUS; PinHeader_1x40_P2.54mm_Vertical
JP1: PINHD-ADDR_FILTER; PinSocket_1x03_P2.54mm_Vertical
JP4: PINHD-POWER/RESET; PinSocket_1x03_P2.54mm_Vertical
Q1: 2N2222 (BC337); TO-92
R1, R2, R7: 1K; R_Axial_DIN0207_L6.3mm_D2.5mm_P10.16mm_Horizontal
R3, R4, R5, R6: 22K; R_Axial_DIN0207_L6.3mm_D2.5mm_P10.16mm_Horizontal
R8, R9, R10, R11: 10K; R_Axial_DIN0207_L6.3mm_D2.5mm_P10.16mm_Horizontal
RIO1: AS6C1008-55PCN; DIP-32_W15.24mm_Socket
RIO_CONTROL1: 74244N; DIP-20_W7.62mm_Socket
RIO_DECODER1: 74245N; DIP-20_W7.62mm_Socket
RN1, RN2, RN3, RN4: 4609M-101-103LF; R_Array_SIP9
U1: FREENOVE_ESP32-WROVER-DEV
Z80-LOCAL_DATA1, Z80-RIO_DATA1, Z80_ADDRHIGH1, Z80_ADDRLOW1: 74245N; DIP-20_W7.62mm_Socket

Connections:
/!CACHE_DATASTATUS: CACHE1.2 (A16), CACHE1.3 (A14), CACHE1.28 (A13), CACHE1.31 (A15), D2.2 (A), D3.2 (A), D4.2 (A), D6.1 (K), D7.1 (K), D7.2 (A), D8.1 (K), D8.2 (A), D9.1 (K), D9.2 (A), D10.1 (K), D10.2 (A), D11.1 (K), D12.1 (K), D13.2 (A), IC1.2 (A1), IC1.3 (Y4), IC1.5 (Y3), IC1.6 (A3), IC1.7 (Y2), IC1.8 (A4), IC1.9 (Y1), IC1.11 (A1), IC1.12 (Y4), IC1.14 (Y3), IC1.15 (A3), IC1.16 (Y2), IC1.17 (A4), IC1.18 (Y1), IC2.3 (I), IC2.5 (I), IC2.9 (I), IC3.5 (Q), IC3.6 (~Q), IC4.8 (O), IC4.10 (I1), IC5.4 (I0), IC5.5 (I1), IC6.10 (CCLR), IC6.12 (CCKEN), IC6.14 (G), IC7.10 (CCLR), IC7.12 (CCKEN), IC7.14 (G), IC8.11 (SCK), IC8.12 (RCK), IC8.13 (G), IC8.14 (SER), IC9.1 (QB), IC9.2 (QC), IC9.3 (QD), IC9.4 (QE), IC9.5 (QF), IC9.6 (QG), IC9.7 (QH), IC9.11 (SCK), IC9.12 (RCK), IC9.13 (G), IC9.15 (QA), IC10.11 (SCK), IC10.12 (RCK), IC10.13 (G), IC11.5 (QF), IC11.6 (QG), IC11.7 (QH), IC11.11 (SCK), IC11.12 (RCK), IC11.13 (G), IC12.1 (SH/~LD), IC12.2 (CLK), IC12.15 (INH), IC13.4 (I0), IC13.5 (I1), IC13.10 (I1), IC13.12 (I0), IC13.13 (I1), IC14.1 (SH/~LD), IC14.2 (CLK), IC14.4 (F), IC14.5 (G), IC14.6 (H), IC14.9 (QH), IC14.15 (INH), IC15.1 (I0), IC15.2 (I1), IC15.3 (O), IC15.4 (I0), IC15.5 (I1), IC15.9 (I0), IC15.10 (I1), IC15.12 (I0), IC15.13 (I1), IC16.1 (SH/~LD), IC16.2 (CLK), IC16.15 (INH), IC17.1 (SH/~LD), IC17.2 (CLK), IC17.3 (E), IC17.4 (F), IC17.5 (G), IC17.6 (H), IC17.11 (A), IC17.12 (B), IC17.13 (C), IC17.14 (D), IC17.15 (INH), IC19.1 (I0), IC19.2 (I1), IC19.4 (I0), IC19.5 (I1), IC19.9 (I0), IC19.10 (I1), IC19.12 (I0), IC19.13 (I1), IC20.1 (I0), IC20.4 (I0), IC20.5 (I1), IC20.12 (I0), IC21.1 (I0), IC21.2 (I1), IC21.4 (I0), IC21.5 (I1), IC21.9 (I0), IC21.10 (I1), IC21.11 (O), IC21.12 (I0), IC22.1 (I0), IC22.4 (I0), IC22.5 (I1), IC22.12 (I0), IC22.13 (I1), J2.1, J2.2, J2.3, J2.4, J2.5, J2.6, J2.7, J2.8, J3.1, J3.2, J3.3, J3.4, J3.5, J3.6, J3.7, J3.8, J4.1, J4.2, J4.3, J4.4, J4.5, J4.6, J4.7, J4.8, J5.6, J5.7, J5.8, J8.2, J8.3, J8.4, J8.5, J8.6, J8.7, J8.8, J8.9, J8.10, J8.11, JP1.2, JP4.1, Q1.1 (C), R2.1, R7.1, R9.1, RIO_CONTROL1.11 (A1), RIO_CONTROL1.13 (A2), RIO_CONTROL1.17 (A4), RIO_DECODER1.11 (B8), RIO_DECODER1.12 (B7), RIO_DECODER1.13 (B6), RIO_DECODER1.14 (B5), RIO_DECODER1.15 (B4), RIO_DECODER1.16 (B3), RIO_DECODER1.17 (B2), RIO_DECODER1.18 (B1), RIO_DECODER1.19 (G), RN1.2, RN1.3, RN1.4, RN1.5, RN1.6, RN1.7, RN3.2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
/CACHE/CACHE_CE2: CACHE1.30 (CE2), R10.1
/CACHE/CACHE_CS: CACHE1.22 (~CE), IC15.11 (O)
/CACHE/CACHE_DATASTATUS+PERM_Z80_IORQ: IC6.11 (CLK), IC6.13 (RCK), IC13.6 (O)
/CACHE/CACHE_OE: CACHE1.24 (~OE), IC15.8 (O)
/CACHE/CACHE_WE: CACHE1.29 (~WE), IC15.6 (O)
/CACHE/LOCAL_ADD_0: CACHE1.12 (A0), IC6.15 (QA), IC10.15 (QA), IC12.11 (A), J6.1, Z80_ADDRLOW1.18 (B1)
/CACHE/LOCAL_ADD_1: CACHE1.11 (A1), IC6.1 (QB), IC10.1 (QB), IC12.12 (B), J6.2, Z80_ADDRLOW1.17 (B2)
/CACHE/LOCAL_ADD_2: CACHE1.10 (A2), IC6.2 (QC), IC10.2 (QC), IC12.13 (C), J6.3, Z80_ADDRLOW1.16 (B3)
/CACHE/LOCAL_ADD_3: CACHE1.9 (A3), IC6.3 (QD), IC10.3 (QD), IC12.14 (D), J6.4, Z80_ADDRLOW1.15 (B4)
/CACHE/LOCAL_ADD_4: CACHE1.8 (A4), IC6.4 (QE), IC10.4 (QE), IC12.3 (E), J6.5, Z80_ADDRLOW1.14 (B5)
/CACHE/LOCAL_ADD_5: CACHE1.7 (A5), IC6.5 (QF), IC10.5 (QF), IC12.4 (F), J6.6, Z80_ADDRLOW1.13 (B6)
/CACHE/LOCAL_ADD_6: CACHE1.6 (A6), IC6.6 (QG), IC10.6 (QG), IC12.5 (G), J6.7, Z80_ADDRLOW1.12 (B7)
/CACHE/LOCAL_ADD_7: CACHE1.5 (A7), IC6.7 (QH), IC10.7 (QH), IC12.6 (H), J6.8, Z80_ADDRLOW1.11 (B8)
/CACHE/LOCAL_ADD_8: CACHE1.27 (A8), IC7.15 (QA), IC11.15 (QA), IC14.11 (A), J5.1, Z80_ADDRHIGH1.18 (B1)
/CACHE/LOCAL_ADD_9: CACHE1.26 (A9), IC7.1 (QB), IC11.1 (QB), IC14.12 (B), J5.2, Z80_ADDRHIGH1.17 (B2)
/CACHE/LOCAL_ADD_10: CACHE1.23 (A10), IC7.2 (QC), IC11.2 (QC), IC14.13 (C), J5.3, Z80_ADDRHIGH1.16 (B3)
/CACHE/LOCAL_ADD_11: CACHE1.25 (A11), IC7.3 (QD), IC11.3 (QD), IC14.14 (D), J5.4, Z80_ADDRHIGH1.15 (B4)
/CACHE/LOCAL_ADD_12: CACHE1.4 (A12), IC11.4 (QE), IC14.3 (E), J5.5, Z80_ADDRHIGH1.14 (B5)
/CACHE/LOCAL_DATA_0: CACHE1.13 (DQ0), IC8.15 (QA), IC16.11 (A), J7.1, RN2.2, Z80-LOCAL_DATA1.18 (B1)
/CACHE/LOCAL_DATA_1: CACHE1.14 (DQ1), IC8.1 (QB), IC16.12 (B), J7.2, RN2.3, Z80-LOCAL_DATA1.17 (B2)
/CACHE/LOCAL_DATA_2: CACHE1.15 (DQ2), IC8.2 (QC), IC16.13 (C), J7.3, RN2.4, Z80-LOCAL_DATA1.16 (B3)
/CACHE/LOCAL_DATA_3: CACHE1.17 (DQ3), IC8.3 (QD), IC16.14 (D), J7.4, RN2.5, Z80-LOCAL_DATA1.15 (B4)
/CACHE/LOCAL_DATA_4: CACHE1.18 (DQ4), IC8.4 (QE), IC16.3 (E), J7.5, RN2.6, Z80-LOCAL_DATA1.14 (B5)
/CACHE/LOCAL_DATA_5: CACHE1.19 (DQ5), IC8.5 (QF), IC16.4 (F), J7.6, RN2.7, Z80-LOCAL_DATA1.13 (B6)
/CACHE/LOCAL_DATA_6: CACHE1.20 (DQ6), IC8.6 (QG), IC16.5 (G), J7.7, RN2.8, Z80-LOCAL_DATA1.12 (B7)
/CACHE/LOCAL_DATA_7: CACHE1.21 (DQ7), IC8.7 (QH), IC16.6 (H), J7.8, RN2.9, Z80-LOCAL_DATA1.11 (B8)
/CORE/!ESP_HARDLOCK: IC1.1 (G), IC2.2 (O)
/CORE/CLR_Z80_HARDLOCK: IC3.1 (CLR), IC5.3 (O)
/CORE/ESP_CONTROL_Z80: D2.1 (K), D3.1 (K), IC1.19 (G)
/CORE/ESP_HARDLOCK: IC2.1 (I), IC13.2 (I1), IC13.9 (I0), U1.26 (GPIO2)
/CORE/ESP_INT: D6.2 (A), D11.2 (A), D12.2 (A), R3.2, R5.2, U1.3 (GPIO36)
/CORE/ESP_WAIT_RESET: C1.1, IC3.13 (CLR), RN1.8, U1.18 (GPIO11)
/CORE/EX_MISO: EX_SPI1.3, U1.13 (GPIO12)
/CORE/EX_MOSI: EX_SPI1.4, U1.15 (GPIO13)
/CORE/EX_SCK: EX_SPI1.2, U1.12 (GPIO14)
/CORE/EX_SS: EX_SPI1.1, U1.25 (GPIO8)
/CORE/PRE_Z80_HARDLOCK: IC3.4 (PRE), IC13.3 (O)
/CORE/SD_CARD_SS: U1.24 (GPIO15), U1.38 (GPIO22)
/CORE/SPIBUS/ESP_SPI.MR: IC8.10 (SCL), IC9.10 (SCL), IC10.10 (SCL), IC11.10 (SCL), R6.2
/CORE/SPIBUS/VCC: D15.2 (A), D16.2 (A), R6.1
/RIO/DEC14: RIO1.3 (A14), RIO_CONTROL1.9 (Y1), RIO_CONTROL1.18 (Y1), RN4.2
/RIO/DEC15: RIO1.31 (A15), RIO_CONTROL1.7 (Y2), RIO_CONTROL1.16 (Y2), RN4.3
/RIO/DEC16: IC20.6 (O), IC20.10 (I1), RIO1.2 (A16), RIO_CONTROL1.1 (G)
/RIO/DEC_CE: IC20.8 (O), RIO1.22 (~CE)
/RIO/DEC_OE: RIO1.24 (~OE), RIO_CONTROL1.3 (Y4), RIO_CONTROL1.12 (Y4), RN4.5, Z80-RIO_DATA1.1 (DIR)
/RIO/DEC_WE: RIO1.29 (~WE), RIO_CONTROL1.5 (Y3), RIO_CONTROL1.14 (Y3), RN4.4
/RIO/ESP_IOD_CONFIG+Z80_WR: IC19.3 (O), RIO_CONTROL1.6 (A3)
/RIO/RIO_CE2: R11.1, RIO1.30 (CE2)
/RIO/ROM_D0: RIO1.13 (DQ0), RIO_DECODER1.2 (A1), Z80-RIO_DATA1.18 (B1)
/RIO/ROM_D1: RIO1.14 (DQ1), RIO_DECODER1.3 (A2), Z80-RIO_DATA1.17 (B2)
/RIO/ROM_D2: RIO1.15 (DQ2), RIO_DECODER1.4 (A3), Z80-RIO_DATA1.16 (B3)
/RIO/ROM_D3: RIO1.17 (DQ3), RIO_DECODER1.5 (A4), Z80-RIO_DATA1.15 (B4)
/RIO/ROM_D4: RIO1.18 (DQ4), RIO_DECODER1.6 (A5), Z80-RIO_DATA1.14 (B5)
/RIO/ROM_D5: RIO1.19 (DQ5), RIO_DECODER1.7 (A6), Z80-RIO_DATA1.13 (B6)
/RIO/ROM_D6: RIO1.20 (DQ6), RIO_DECODER1.8 (A7), Z80-RIO_DATA1.12 (B7)
/RIO/ROM_D7: RIO1.21 (DQ7), RIO_DECODER1.9 (A8), Z80-RIO_DATA1.11 (B8)
/RIO/ROM_D_RDY: IC19.8 (O), IC20.13 (I1), RIO_CONTROL1.19 (G), Z80-RIO_DATA1.19 (G)
/RIO/ROM_WR_PROTECT+Z80_WR: IC19.11 (O), RIO_CONTROL1.15 (A3)
/RIO/Z80_A0: J8.20, JP1.3, RIO1.12 (A0), Z80_ADDRLOW1.2 (A1)
/RIO/Z80_A1: J8.21, RIO1.11 (A1), Z80_ADDRLOW1.3 (A2)
/RIO/Z80_A2: J8.22, RIO1.10 (A2), Z80_ADDRLOW1.4 (A3)
/RIO/Z80_A3: J8.23, RIO1.9 (A3), Z80_ADDRLOW1.5 (A4)
/RIO/Z80_A4: J8.24, RIO1.8 (A4), Z80_ADDRLOW1.6 (A5)
/RIO/Z80_A5: J8.25, RIO1.7 (A5), Z80_ADDRLOW1.7 (A6)
/RIO/Z80_A6: J8.26, RIO1.6 (A6), Z80_ADDRLOW1.8 (A7)
/RIO/Z80_A7: J8.27, RIO1.5 (A7), Z80_ADDRLOW1.9 (A8)
/RIO/Z80_A8: J8.28, RIO1.27 (A8), Z80_ADDRHIGH1.2 (A1)
/RIO/Z80_A9: J8.29, RIO1.26 (A9), Z80_ADDRHIGH1.3 (A2)
/RIO/Z80_A10: J8.30, RIO1.23 (A10), Z80_ADDRHIGH1.4 (A3)
/RIO/Z80_A11: J8.31, RIO1.25 (A11), Z80_ADDRHIGH1.5 (A4)
/RIO/Z80_A12: J8.32, RIO1.4 (A12), Z80_ADDRHIGH1.6 (A5)
/RIO/Z80_A13: J8.33, RIO1.28 (A13), Z80_ADDRHIGH1.7 (A6)
/RIO/Z80_A14: J8.34, RIO_CONTROL1.2 (A1), Z80_ADDRHIGH1.8 (A7)
/RIO/Z80_A15: J8.35, RIO_CONTROL1.4 (A2), Z80_ADDRHIGH1.9 (A8)
/RIO/Z80_D0: J8.12, Z80-LOCAL_DATA1.2 (A1), Z80-RIO_DATA1.2 (A1)
/RIO/Z80_D1: J8.13, Z80-LOCAL_DATA1.3 (A2), Z80-RIO_DATA1.3 (A2)
/RIO/Z80_D2: J8.14, Z80-LOCAL_DATA1.4 (A3), Z80-RIO_DATA1.4 (A3)
/RIO/Z80_D3: J8.15, Z80-LOCAL_DATA1.5 (A4), Z80-RIO_DATA1.5 (A4)
/RIO/Z80_D4: J8.16, Z80-LOCAL_DATA1.6 (A5), Z80-RIO_DATA1.6 (A5)
/RIO/Z80_D5: J8.17, Z80-LOCAL_DATA1.7 (A6), Z80-RIO_DATA1.7 (A6)
/RIO/Z80_D6: J8.18, Z80-LOCAL_DATA1.8 (A7), Z80-RIO_DATA1.8 (A7)
/RIO/Z80_D7: J8.19, Z80-LOCAL_DATA1.9 (A8), Z80-RIO_DATA1.9 (A8)
/RIO/Z80_RD+ESP_IOD_CONFIG+PERM_Z80_IORQ: IC20.3 (O), RIO_CONTROL1.8 (A4)
/Z80 BUS/Z80_ADD_DIR: IC22.6 (O), Z80_ADDRHIGH1.1 (DIR), Z80_ADDRLOW1.1 (DIR)
/Z80 BUS/Z80_ADD_OE: IC22.3 (O), Z80_ADDRHIGH1.19 (G), Z80_ADDRLOW1.19 (G)
/Z80 BUS/Z80_DATA_DIR: IC22.8 (O), Z80-LOCAL_DATA1.1 (DIR)
/Z80 BUS/Z80_DATA_OE: IC22.11 (O), Z80-LOCAL_DATA1.19 (G)
GND: C1.2, C2.2, C3.2, C4.2, C5.2, CACHE1.16 (VSS), D1.2 (A), EX_SPI1.6, IC16.10 (SER), JP1.1, JP4.2, Q1.3 (E), R5.1, RIO1.16 (VSS), U1.14 (GND), U1.21 (GND), U1.34 (GND), U1.40 (GND)
unnamed: D1.1 (K), R1.1
unnamed: D4.1 (K), U1.35 (GPIO21)
unnamed: D5.1 (K), RN1.1
unnamed: D13.1 (K), IC3.8 (~Q)
unnamed: D14.1 (K), RN4.1
unnamed: D15.1 (K), RN2.1
unnamed: D16.1 (K), RN3.1
unnamed: IC2.6 (O), IC5.2 (I1)
unnamed: IC2.8 (O), IC3.10 (PRE)
unnamed: IC2.11 (I), IC5.6 (O)
unnamed: IC2.10 (O), IC4.9 (I0)
unnamed: C2.1, IC5.1 (I0), R4.2
unnamed: IC6.9 (RCO), IC7.11 (CLK), IC7.13 (RCK)
unnamed: IC8.9 (QH*), IC9.14 (SER)
unnamed: IC10.9 (QH*), IC11.14 (SER)
unnamed: IC9.9 (QH*), IC10.14 (SER)
unnamed: IC12.9 (QH), IC14.10 (SER)
unnamed: IC12.10 (SER), IC17.9 (QH)
unnamed: IC2.4 (O), IC13.1 (I0)
unnamed: IC13.8 (O), IC21.13 (I1)
unnamed: IC1.4 (A2), IC1.13 (A2), IC13.11 (O)
unnamed: IC16.9 (QH), IC17.10 (SER)
unnamed: IC19.6 (O), IC20.2 (I1)
unnamed: IC20.9 (I0), IC20.11 (O)
unnamed: IC21.3 (O), IC22.2 (I1)
unnamed: IC21.6 (O), IC22.9 (I0)
unnamed: IC21.8 (O), IC22.10 (I1)
unnamed: Q1.2 (B), R2.2
unnamed: R8.1, RIO_DECODER1.1 (DIR)
VCC: C3.1, C4.1, C5.1, CACHE1.32 (VCC), D5.2 (A), D14.2 (A), EX_SPI1.5, JP4.3, R1.2, R3.1, R4.1, R7.2, R8.2, R9.2, R10.2, R11.2, RIO1.32 (VCC), U1.19 (+5v), U1.20 (+5V)
